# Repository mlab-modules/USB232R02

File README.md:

# USB232R02A
The module USB232R02A is a versatile and high-quality converter from USB to serial UART with 3.3V CMOS drive output and TTL input. It features a 5V-tolerant input and utilizes the reliable FT231XQ chip from FTDI The converter uses [FT231XQ](https://ftdichip.com/products/ft231xq/) chip from FTDI, ensuring maximum compatibility with all major operating systems. With supports for Full Speed USB and Full Handshake UART signals. 

The module provides the ability to power your devices via 5V from USB and 3.3V from the integrated power source simultaneously. The protection of the host device for overcurrent is realized by reversible fuse (750mA). 5V header is powerd from USB bus (trought fuse). The 3.3V power source is supplied from an LDO integrated in the FTDI converter. The 3.3V current limit is 50mA.

## What makes this module special?

USB23202A is differ from other USB-UART converters with its compatibility with MLAB standards, this fact will save any engineer or maker o lot of time. One of its key features is a unified dimension and pattern of M3 mounting screws that can be used to create a solid foundation and ground plane for your complex designs, thanks to its aluminum mounting board ALBASEx. This not only ensures mechanical durability but also makes it easy to mount your device into your final designs. With uniform cable wiring methods, this device protects your design from unnecessary malfunctions, providing you with a tool to easily and quickly prototype your high-quality devices. Invest in the USB23202A and take your designs to the next level!

## Parameters

| Parameter | Value | Description |
|-----------|-------|-------------|
| Dimensions | 40,132 x 29,972 mm | PCB dimensions |
| IO | FT231XQ | Original FTDI | 
| Number of UART channels | 1 | Including all control signals | 
| USB speed | Full Speed (12 Mbps) | |
| USB connector | USB-B | USB 2.0 |
| Communication indication | 2x LED UART RX/TX | Purpose of LEDs can be changed |
| USB Class | FTDI driver | Virtual COM port |
| Power source | 5V and 3.3V (50mA) | 3.3V is provided by FT231XQ |

## How to get this device? 

This device is sold by [Universal Scientific Technologies s.r.o.](https://www.ust.cz). If you are interested in our equipment, do not be afraid to [contact us](mailto:sale@ust.cz).

## Schematics

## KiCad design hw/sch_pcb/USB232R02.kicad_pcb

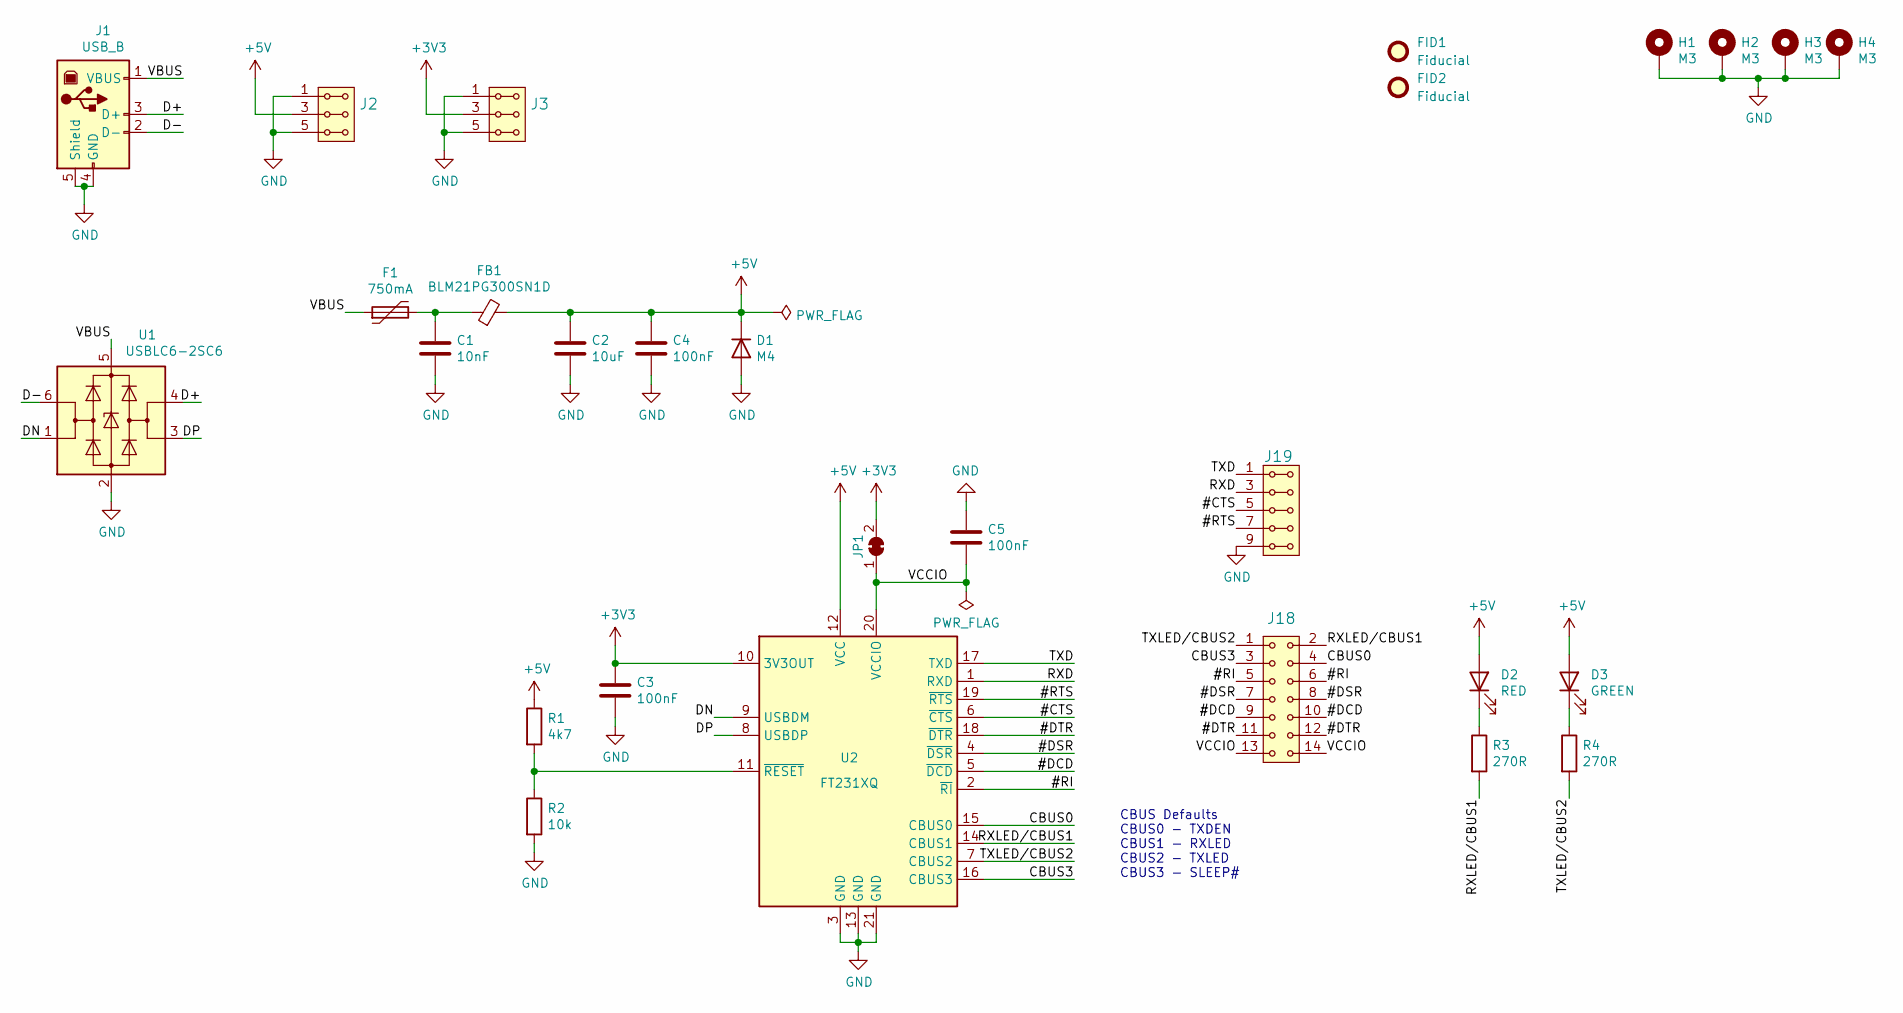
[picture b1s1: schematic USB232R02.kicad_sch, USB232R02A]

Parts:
C1: 10nF; SMD-0805; LCSC C913645
C2: 10uF; SMD-0805; LCSC C17024
C3, C4, C5: 100nF; SMD-0805; LCSC C111492
D1: M4; D_SMA; LCSC C466506
D2: RED; LED_1206_2; LCSC C598398
D3: GREEN; LED_1206_2; LCSC C598394
F1: 750mA; 1812; LCSC C269130
FB1: BLM21PG300SN1D; SMD-0805; LCSC C16903
FID1, FID2: Fiducial; Fiducial_1mm_Mask2mm
H1, H2, H3, H4: M3; MountingHole_3mm
J1: USB_B; USB_B_OST_USB-B1HSxx_Horizontal; LCSC C490687
J2, J3: HEADER_2x03; Straight_2x03; LCSC C706893
J18: HEADER_2x07; Straight_2x07; LCSC C706897
J19: HEADER_2x05; Straight_2x05; LCSC C706895
JP1: SolderJumper_2_Bridged; SolderJumper-2_P1.3mm_Bridged_RoundedPad1.0x1.5mm
R1: 4k7; SMD-0805; LCSC C60816
R2: 10k; SMD-0805; LCSC C84376
R3, R4: 270R; SMD-0805; LCSC C228675
U1: USBLC6-2SC6; SOT-23-6; LCSC C7519
U2: FT231XQ; QFN-20-1EP_4x4mm_P0.5mm_EP2.5x2.5mm; LCSC C132159

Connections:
+3V3: C3.1, J3.3, J3.4, JP1.2 (B), U2.10 (3V3OUT)
+5V: C2.1, C4.1, D1.1 (K), D2.2 (A), D3.2 (A), FB1.2, J2.3, J2.4, R1.1, U2.12 (VCC)
/#CTS: J19.5, J19.6, U2.6 (~CTS)
/#DCD: J18.9, J18.10, U2.5 (~DCD)
/#DSR: J18.7, J18.8, U2.4 (~DSR)
/#DTR: J18.11, J18.12, U2.18 (~DTR)
/#RI: J18.5, J18.6, U2.2 (~RI)
/#RTS: J19.7, J19.8, U2.19 (~RTS)
/CBUS0: J18.4, U2.15 (CBUS0)
/CBUS3: J18.3, U2.16 (CBUS3)
/D+: J1.3 (D+), U1.4 (I/O2)
/D-: J1.2 (D-), U1.6 (I/O1)
/DN: U1.1 (I/O1), U2.9 (USBDM)
/DP: U1.3 (I/O2), U2.8 (USBDP)
/RXD: J19.3, J19.4, U2.1 (RXD)
/RXLED/CBUS1: J18.2, R3.2, U2.14 (CBUS1)
/TXD: J19.1, J19.2, U2.17 (TXD)
/TXLED/CBUS2: J18.1, R4.2, U2.7 (CBUS2)
/VBUS: F1.1, J1.1 (VBUS), U1.5 (VBUS)
/VCCIO: C5.2, J18.13, J18.14, JP1.1 (A), U2.20 (VCCIO)
GND: C1.2, C2.2, C3.2, C4.2, C5.1, D1.2 (A), H1.1, H2.1, H3.1, H4.1, J1.4 (GND), J1.5 (Shield), J2.1, J2.2, J2.5, J2.6, J3.1, J3.2, J3.5, J3.6, J19.9, J19.10, R2.2, U1.2 (GND), U2.3 (GND), U2.13 (GND), U2.21 (GND)
unnamed: C1.1, F1.2, FB1.1
unnamed: D2.1 (K), R3.1
unnamed: D3.1 (K), R4.1
unnamed: R1.2, R2.1, U2.11 (~RESET)

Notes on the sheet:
CBUS Defaults CBUS0 - TXDEN CBUS1 - RXLED CBUS2 - TXLED CBUS3 - SLEEP#

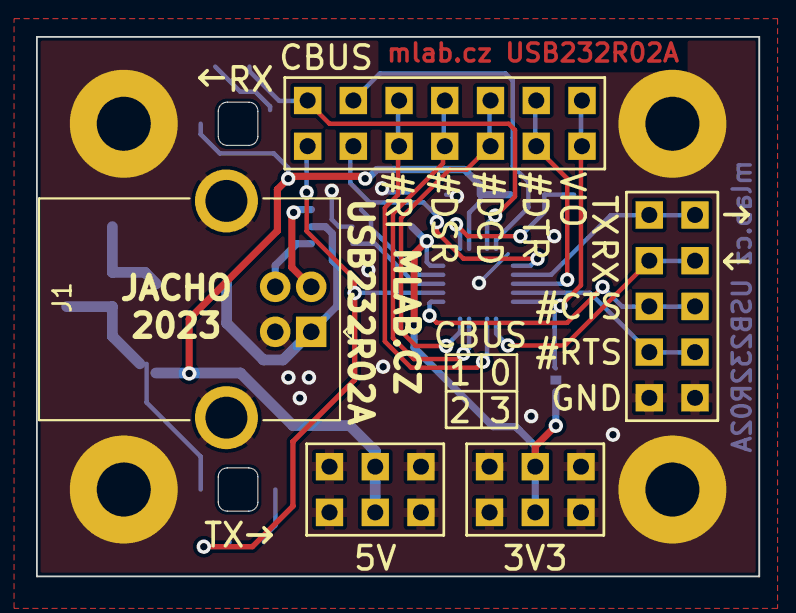
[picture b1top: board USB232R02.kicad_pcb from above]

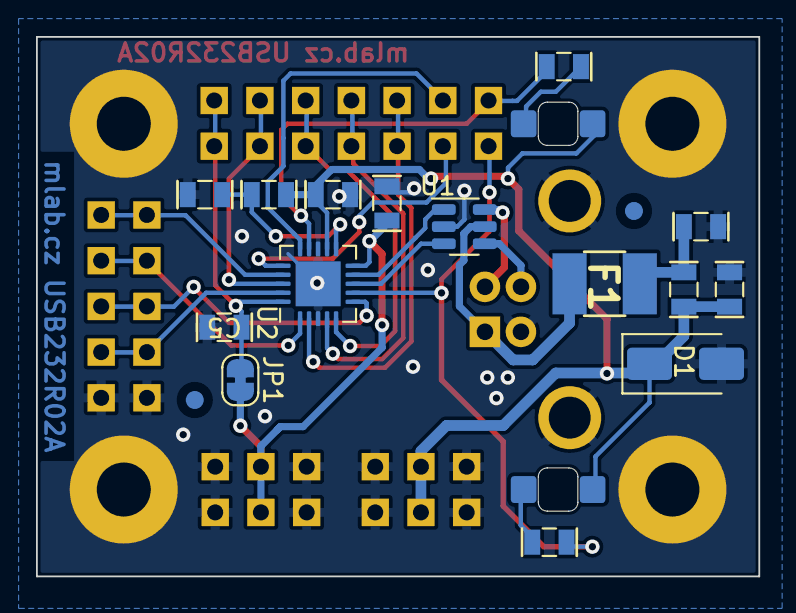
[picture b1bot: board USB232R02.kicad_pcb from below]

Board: 2 copper layers, 40.1 x 30.0 mm, 28 parts (19 on the bottom side), 25 nets.

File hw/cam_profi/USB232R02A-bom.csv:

Component,Description,Part,References,Value,Footprint,Quantity Per PCB,Datasheet,lcsc,ust_id
1,Unpolarized capacitor,C,C1,10nF,SMD-0805,1,~,C913645,5c70984712875079b91f8b49
2,Unpolarized capacitor,C,C3 C4 C5,100nF,SMD-0805,3,~,C111492,5c70984712875079b91f8b4c
3,Unpolarized capacitor,C,C2,10uF,SMD-0805,1,~,C17024,5c70984812875079b91f8bbd
4,Light emitting diode,LED,D3,GREEN,LED_1206_2,1,https://www.tme.eu/Document/283cf8402cc8d70fa16840405395cb5a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,C598394,5c70984412875079b91f8895
5,Diode,D,D1,M4,D_SMA,1,~,C466506,5c70984512875079b91f88ac
6,Light emitting diode,LED,D2,RED,LED_1206_2,1,http://www.kingbright.com/attachments/file/psearch/000/00/20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,C598398,5c70984412875079b91f8896
7,"Resettable fuse, polymeric positive temperature coefficient",Polyfuse,F1,750mA,1812,1,~,C269130,5c70984512875079b91f88d2
8,"Ferrite bead, small symbol",FerriteBead_Small,FB1,BLM21PG300SN1D,SMD-0805,1,~,C16903,5c70984412875079b91f87fd
9,"2x03 2.54 mm pitch header, 2 pins next to each other are connected",HEADER_2x03_PARALLEL,J2 J3,HEADER_2x03,Straight_2x03,2,,C706893,
10,"2x05 2.54 mm pitch header, 2 pins next to each other are connected",HEADER_2x05_PARALLEL,J19,HEADER_2x05,Straight_2x05,1,,C706895,
11,2x07 2.54 mm pitch header,HEADER_2x07,J18,HEADER_2x07,Straight_2x07,1,,C706897,
12,USB Type B connector,USB_B,J1,USB_B,USB_B_OST_USB-B1HSxx_Horizontal,1, ~,C490687,5c70984412875079b91f87a8
13,Resistor,R,R3 R4,270R,SMD-0805,2,~,C228675,5c70984512875079b91f8983
14,Resistor,R,R1,4k7,SMD-0805,1,~,C60816,5c70984612875079b91f8995
15,Resistor,R,R2,10k,SMD-0805,1,~,C84376,5c70984612875079b91f899f
16,"Full Speed USB to Full Handshake UART, QFN-20",FT231XQ,U2,FT231XQ,QFN-20-1EP_4x4mm_P0.5mm_EP2.5x2.5mm,1,https://www.ftdichip.com/Support/Documents/DataSheets/ICs/DS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,C132159,605d7fe0128750769e769adb
17,"Very low capacitance ESD protection diode, 2 data-line, SOT-23-6",USBLC6-2SC6,U1,USBLC6-2SC6,SOT-23-6,1,https://www.st.com/resource/en/datasheet/usblc6-2.pdf,C7519,5e82e0691287502a334a778c





Component Groups:,17
Component Count:,21
Fitted Components:,21
Number of PCBs:,1
Total components:,21
Schematic Version:,
Schematic Date:,2021-03-25
PCB Variant:,default
BoM Date:,Fri Jul  7 15:51:51 2023
Schematic Source:,USB232R02.kicad_sch
KiCad Version:,Eeschema 7.0.5.1-1-g8f565ef7f0-dirty-deb11

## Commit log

2020-11-29 Zalozeni struktury.
2020-11-29 Přidán dokumentační list IO.
2020-11-30 Edit
2020-12-02 Oprava složkové struktury.
2020-12-02 Automation
2021-03-25 Add MLAB title block. Minor layout cleanup Cleanup silkscreen.
2022-04-06 automated commit; add github actions
2022-04-06 Update actions products
2022-05-21 Edit PCB
2022-05-21 aktualizace actions
2022-05-22 Oprava actions
2022-05-22 vyreseni DRC, uprava sablon
2022-05-22 Úprava potisku
2022-05-25 Priprava pro osazeni.
2022-06-14 Update title block and resolve ERC issues.
2022-09-23 Swap mounting holes from top to bottom, to allow its use for aligment in PnP data output.
2022-09-23 Add PnP project files.
2022-09-27 PnP job configuration update.
2022-09-27 Add place job to location which is not deleted by github actions.
2022-09-27 unucessfull attempt to set board panel
2022-09-27 new attempt to set PCB panel.
2022-10-03 Update job file according real position of board.
2022-10-03 Set Z coordinate of board.
2023-01-29 submodule update
2023-02-08 update assets
2023-02-08 rename files
2023-02-08 rename output
2023-02-09 update submodule
2023-02-09 Kibot update (#2)
    * Update kicad_outputs.yml
    * Update actions products
    * submodule update
    * Update kicad_outputs.yml
    * Update actions products
    * Update kicad_outputs.yml
2023-02-14 update actions
2023-02-14 Update metadata files
2023-02-14 Update workflow files
2023-04-25 Test of different setups of PCB panel. Prior introducing the panel fiducials.
2023-04-25 The first setup of panel fiducials. Unworking state.
2023-07-05 automated commit; rename source files to new naming convence
2023-07-07 clean repo, update kicad footprints, prepare to assembly
2023-07-07 aktualizace kodu a konfigurace
2023-09-07 Working openpnp job file
2023-09-07 add pnp related files
2023-09-16 Update status
